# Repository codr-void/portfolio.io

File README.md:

# Engineering Portfolio

This repository is a comprehensive engineering portfolio covering **Embedded Systems**, **SoC Design**, **IC Design**, **Operating Systems / Kernel Development**, and **Hardware–Software Co-Design**.  
It contains academic and personal projects with full documentation, schematics, source code, and reports.

---

## 🔹 Featured Projects

### 🚗 Parking_BCB — Smart Parking Counter System
**Embedded Systems | Hardware–Software Co-Design**

A complete embedded product designed to monitor and count available parking spaces.

**Highlights**
- Arduino-based embedded firmware
- Custom PCB designed in **KiCad**
- IR sensor subsystem
- Solar-powered considerations
- Full documentation: BOM, schematics, test plans, and 3D models

📁 `Parking_BCB/`  
📄 Includes final firmware, PCB files, STL models, and reports.

---

### 📡 RISC-V Based 5G IIoT Hub
**SoC Design | Embedded | IIoT**

A conceptual **5G-enabled Industrial IoT hub** integrating embedded control and communication.

**Highlights**
- RISC-V based SoC concept
- 5G module integration (Arduino prototype)
- Motor control (C)
- System-level architecture and proposal

📁 `SoC_Design/5G_IIoT_Hub/`  
📄 Proposal and system documentation included.

---

### ⚙️ Cache Simulator
**Computer Architecture | C Programming**

A cache memory simulator written in C.

**Highlights**
- Configurable cache parameters
- Test vectors and output logs
- Makefile-based build

📁 `cache_simulator/`

---

## 🧠 Embedded Systems

📁 `Embedded_Systems/`

Includes multiple embedded and robotics projects:

- **Aeroponics System** — system design and control documentation
- **ARM Assembly** — low-level ARM assembly programs and analysis
- **Robotic Arm** — kinematic modeling and visualization
- **Robotic Car**
  - Vision-based color detection and sorting
  - Mecanum wheel control
  - Camera calibration
  - Obstacle avoidance
  - Python-based control stack

This section demonstrates hands-on experience with **microcontrollers, robotics, sensors, and control software**.

---

## 🔬 IC Design & VLSI

📁 `IC_design/`

CMOS and analog IC design projects developed using **Cadence Virtuoso**.

**Highlights**
- CMOS inverters (short & long channel)
- Resistive inverter design
- Compound CMOS logic gates
- DC and transient analysis
- Complete schematics, symbols, and simulation data

📄 Reports and PDFs included for each design.

---

## 🧩 Kernel & Operating Systems

📁 `Kernel_and_OS/`

**Highlights**
- Linux kernel module development
- Character device driver
- User–kernel space interaction
- GNU/Linux fundamentals
- Kernel build artifacts and reports

Includes both **educational experiments** and **functional kernel code**.

---

## 🎛️ Analog Circuits

📁 `op_amp_filters/Sound_Filter/`

- Low-pass, high-pass, and band-pass audio filters
- Operational amplifier based designs
- Measurement results and final report

---

## 🌐 Web & Visualization

📁 `Kernel_and_OS/Websites/`

- Interactive HTML map project
- JavaScript-based geographic visualization
- Academic project documentation

---

## 🧪 Other Engineering Projects

📁 `other/`

- **Mars Rover** — conceptual mechanical/system design
- **Water Filter** — engineering poster and documentation

---

## 🛠️ Skills Demonstrated

- Embedded C / Arduino / Python
- PCB design (KiCad)
- SoC & RISC-V concepts
- IC design (CMOS, analog)
- Linux kernel development
- Robotics & computer vision
- Hardware–software integration
- Technical documentation

---

## 📌 Notes

- This repository reflects **academic, lab, and project-based work**
- Each major project contains its own documentation and reports
- File structure is preserved as originally developed

---

📫 **Contact**  
If you’re reviewing this repository for academic or professional purposes, feel free to reach out via GitHub.

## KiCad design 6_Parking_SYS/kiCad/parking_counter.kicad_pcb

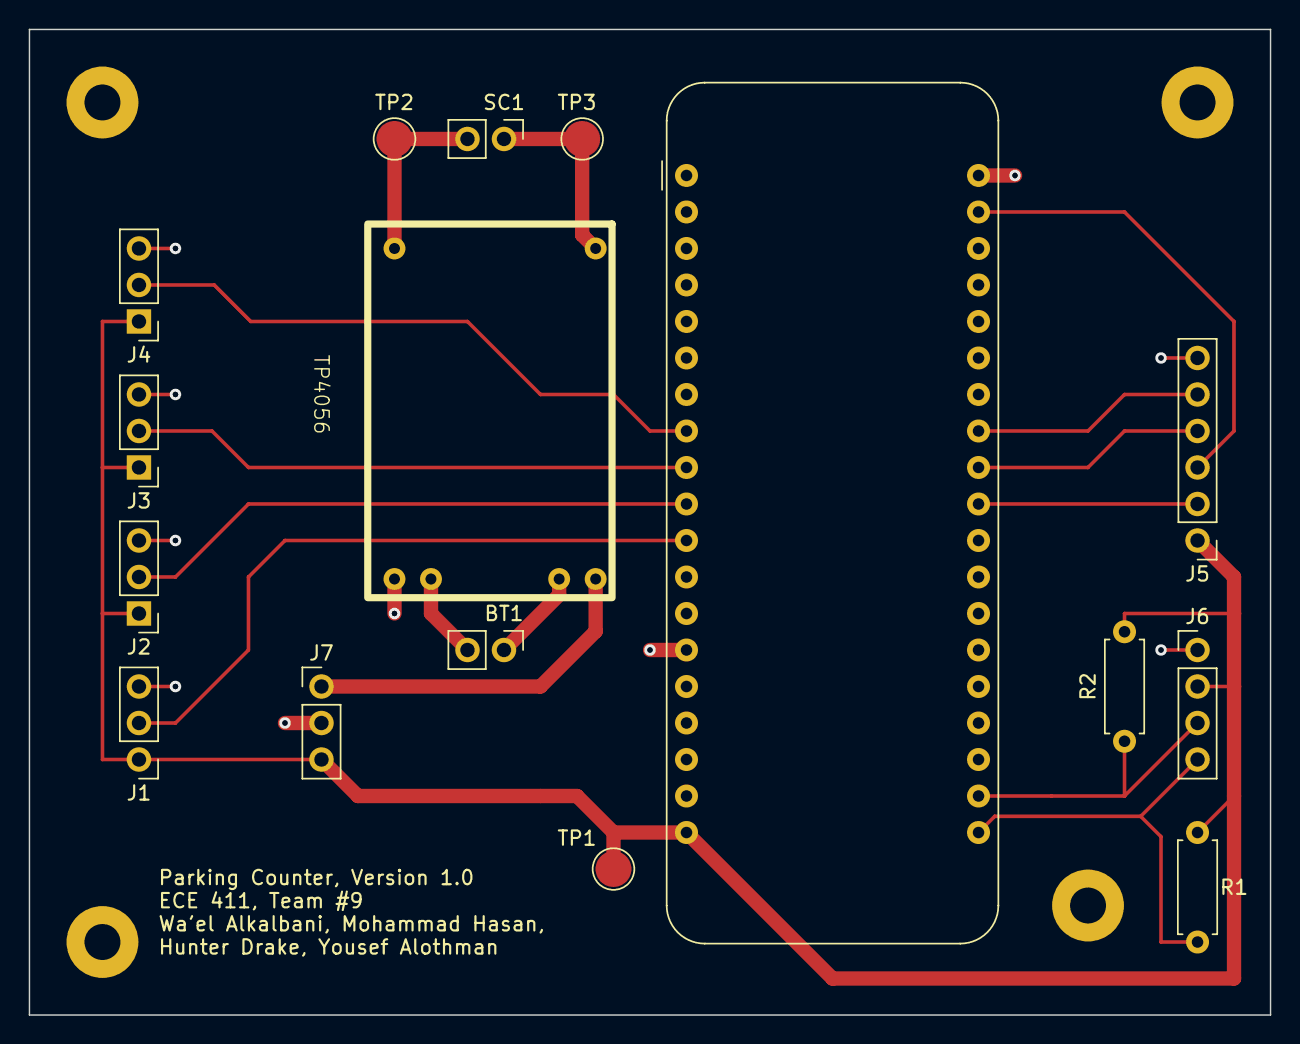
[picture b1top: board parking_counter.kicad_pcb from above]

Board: 2 copper layers, 86.4 x 68.6 mm, 16 parts (0 on the bottom side), 17 nets.

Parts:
BT1: 3V7 Battery; PinHeader_1x02_P2.54mm_Vertical
J1, J2, J3, J4: IR SENSOR 1; PinHeader_1x03_P2.54mm_Vertical
J5: Micro_SD; PinHeader_1x06_P2.54mm_Vertical
J6: 16x2 LCD SCREEN w/I2C; PinHeader_1x04_P2.54mm_Vertical
J7: Comdix; PinHeader_1x03_P2.54mm_Vertical
R1, R2: R10k; R_Axial_DIN0207_L6.3mm_D2.5mm_P7.62mm_Horizontal
SC1: 5V Solar Cell; PinHeader_1x02_P2.54mm_Vertical
TP1, TP2, TP3: TestPoint; TestPoint_Pad_D2.5mm
TP4056: TP4056
U1: HiLetgo ESP-WROOM-32S; Adafruit_Feather_WithMountingHoles

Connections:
+5V: J1.1 (VCC), J2.1 (VCC), J3.1 (VCC), J4.1 (VCC), J5.1 (+5V), J6.2 (VCC), J7.3 (V_OUT), R1.1, R2.1, TP1.1, U1.19 (5V)
GND: J1.3 (GND), J2.3 (GND), J3.3 (GND), J4.3 (GND), J5.6 (GND), J6.1 (GND), J7.2 (GND), TP4056.4 (VBUS-), U1.14 (GND), U1.38 (GND)
unnamed: BT1.1 (BAT+), TP4056.2 (BAT+)
unnamed: BT1.2 (BAT-), TP4056.3 (BAT-)
unnamed: J1.2 (OUT), U1.11 (IO27)
unnamed: J2.2 (OUT), U1.10 (IO26)
unnamed: J3.2 (OUT), U1.9 (IO25)
unnamed: J4.2 (OUT), U1.8 (IO33)
unnamed: J5.4 (CLK), U1.30 (IO18)
unnamed: J5.2 (CS), U1.29 (IO5)
unnamed: J5.5 (MISO), U1.31 (IO19)
unnamed: J5.3 (MOSI), U1.37 (IO23)
unnamed: J6.4 (SCL), R1.2, U1.20 (CLK)
unnamed: J6.3 (SDA), R2.2, U1.21 (SD0)
unnamed: J7.1 (V_IN), TP4056.1 (VBUS+)
unnamed: SC1.1 (SOLAR+), TP3.1, TP4056.5 (SOLAR+)
unnamed: SC1.2 (SOLAR-), TP2.1, TP4056.6 (SOLAR-)

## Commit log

2024-02-14 updated by Wa'el
2024-02-14 Add projects files
2024-02-14 Configure Git LFS
2024-02-14 updated rebo
2024-05-05 Update README.txt
    added senior year capstone
2024-05-05 python prg
2024-05-05 index no. added
2024-05-06 Configure LFS tracking
2024-05-06 robotic car source code
2026-01-29 Reorganized repository structure and categorized flagship projects
2026-01-29 Reorganized repository
